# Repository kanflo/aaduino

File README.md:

# The AAduino

### News! Don't miss the successor of the AAduino, the [AAduino Zero](https://github.com/kanflo/aaduino-zero).

The AAduino is an wireless Arduino clone the size of an AA battery with Keystone battery terminals rotated 180° to act as positive and negative terminals. It is meant to go inside a 3xAA battery holder creating a very small wireless node.

Powered by an ATMega328p, it is fitted with an RFM69CW companion, two DS18B20 temperature sensors and an indicator LED.

Included in this repository is the schematics, bill of material and a sample program to test the hardware.
If you want solder up one yourself you can buy most of what is needed through the links on the [Kitnic page](https://kitnic.it/boards/github.com/kanflo/aaduino).

If you are looking for an easy way to order the PCBs only, please order from [DirtyPCBs.com](http://dirtypcbs.com/view.php?share=18116&accesskey=5cb9ea9c4754e5c9102b4350393b244e) and I will receive a $1 credit :)

The accompanying blog post is [here](http://johan.kanflo.com/the-aaduino).

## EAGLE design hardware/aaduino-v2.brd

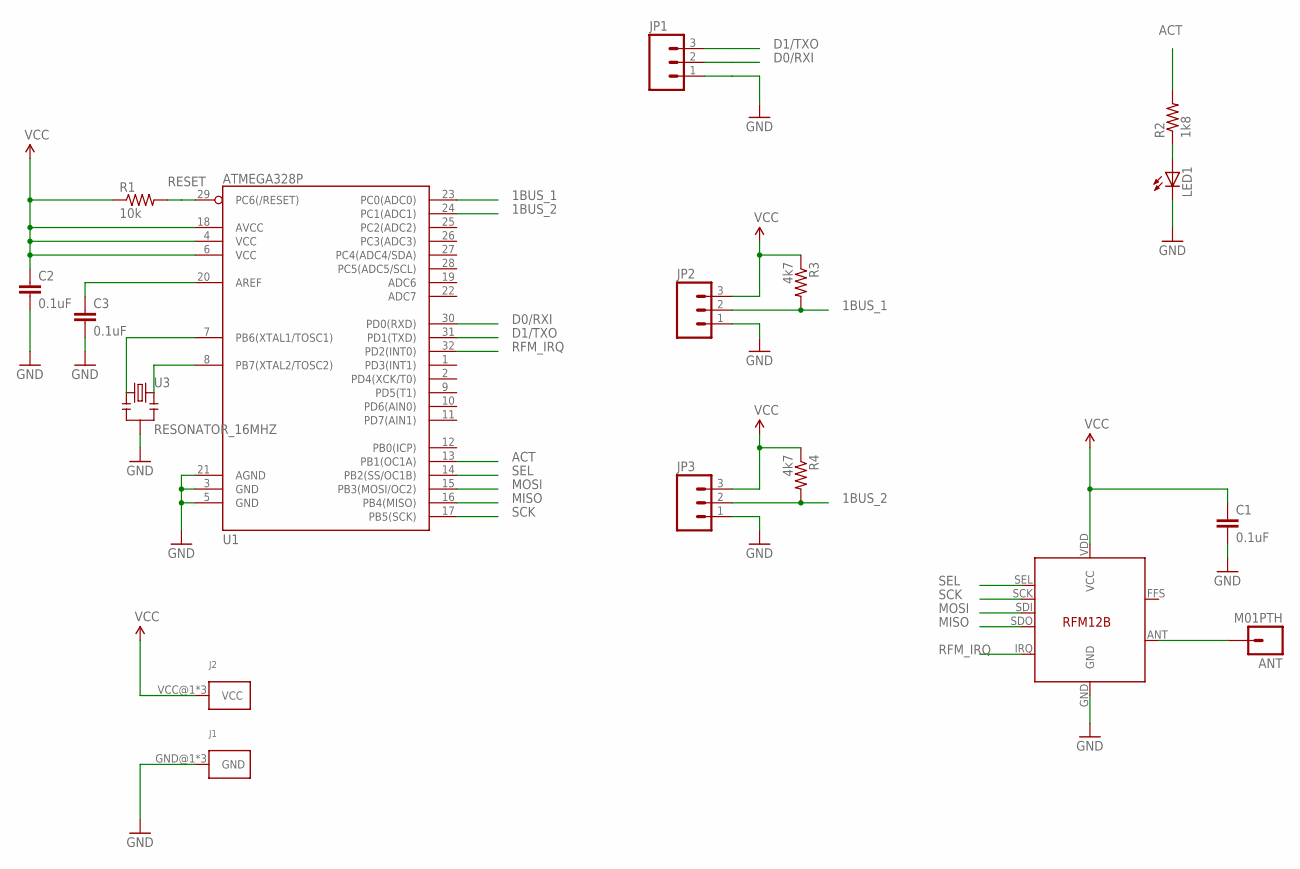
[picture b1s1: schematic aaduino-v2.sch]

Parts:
ANT: M01PTH; 1X01
C1, C2, C3: 0.1uF; 0603-CAP
J1: KEYSTONE-629; KEYSTONE_AA_AAA_BATTERY_TERMINAL-629
J2: KEYSTONE-637; KEYSTONE_AA_AAA_BATTERY_TERMINAL-637
JP1, JP2, JP3: M03PTH; 1X03
LED1: LED0603; LED-0603
R1: 10k; 0603-RES
R2: 1k8; 0603-RES
R3, R4: 4k7; 0603-RES
U1: ATMEGA328P; TQFP32-08
U2: RFM12B
U3: RESONATOR_16MHZ; RESONATOR_SMD

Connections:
1BUS_1: JP2.2, R3.2, U1.23 (PC0(ADC0))
1BUS_2: JP3.2, R4.2, U1.24 (PC1(ADC1))
ACT: R2.2, U1.13 (PB1(OC1A))
D0/RXI: JP1.2, U1.30 (PD0(RXD))
D1/TXO: JP1.3, U1.31 (PD1(TXD))
GND: C1.2, C2.2, C3.2, J1.GND@1, J1.GND@2, J1.GND@3, JP1.1, JP2.1, JP3.1, LED1.C, U1.3 (GND), U1.5 (GND), U1.21 (AGND), U2.GND, U3.2
MISO: U1.16 (PB4(MISO)), U2.SDO
MOSI: U1.15 (PB3(MOSI/OC2)), U2.SDI
unnamed: LED1.A, R2.1
unnamed: C3.1, U1.20 (AREF)
unnamed: U1.7 (PB6(XTAL1/TOSC1)), U3.1
unnamed: U1.8 (PB7(XTAL2/TOSC2)), U3.3
unnamed: ANT.1, U2.ANT
RESET: R1.2, U1.29 (PC6(/RESET))
RFM_IRQ: U1.32 (PD2(INT0)), U2.IRQ
SCK: U1.17 (PB5(SCK)), U2.SCK
SEL: U1.14 (PB2(SS/OC1B)), U2.SEL
VCC: C1.1, C2.1, J2.VCC@1, J2.VCC@2, J2.VCC@3, JP2.3, JP3.3, R1.1, R3.1, R4.1, U1.4 (VCC), U1.6 (VCC), U1.18 (AVCC), U2.VDD (VCC)

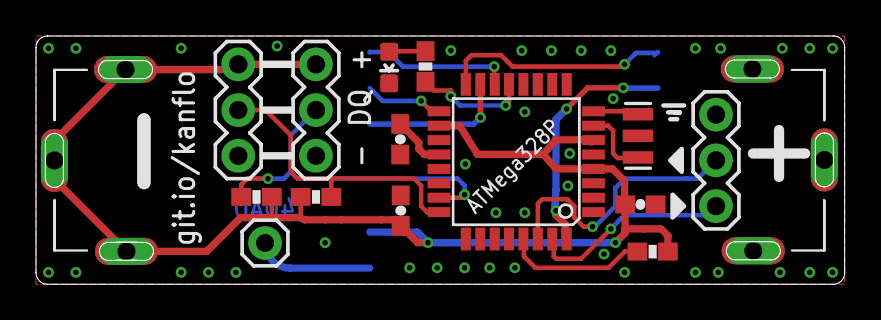
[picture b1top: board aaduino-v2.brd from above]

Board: 2 copper layers, 44.9 x 13.8 mm, 17 parts (1 on the bottom side), 18 nets.

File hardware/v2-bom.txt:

Part Value           Device                    Package                              Description           PROD_ID   VALUE     
ANT  M01PTH          M01PTH                    1X01                                 Header 1                                  
C1   0.1uF           0.1UF-25V(+80/-20%)(0603) 0603-CAP                             CAP-00810             CAP-00810 0.1uF     
C2   0.1uF           0.1UF-25V(+80/-20%)(0603) 0603-CAP                             CAP-00810             CAP-00810 0.1uF     
C3   0.1uF           0.1UF-25V(+80/-20%)(0603) 0603-CAP                             CAP-00810             CAP-00810 0.1uF     
J1   KEYSTONE-629    KEYSTONE-629              KEYSTONE_AA_AAA_BATTERY_TERMINAL-629 Keystone 629                              
J2   KEYSTONE-637    KEYSTONE-637              KEYSTONE_AA_AAA_BATTERY_TERMINAL-637 Keystone 637                              
JP1                  M03PTH                    1X03                                 Header 3                                  
JP2                  M03PTH                    1X03                                 Header 3                                  
JP3                  M03PTH                    1X03                                 Header 3                                  
LED1                 LED0603                   LED-0603                             LEDs                                      
R1   10k             RESISTOR0603-RES          0603-RES                             Resistor                                  
R2   1k8             RESISTOR0603-RES          0603-RES                             Resistor                                  
R3   4k7             RESISTOR0603-RES          0603-RES                             Resistor                                  
R4   4k7             RESISTOR0603-RES          0603-RES                             Resistor                                  
U1   ATMEGA328P      ATMEGA328_SMT             TQFP32-08                            32-Pin Atmega328 part IC-09069  ATMEGA328P
U2   RFM12B          RFM12B                    RFM12B                                                                         
U3   RESONATOR_8MHZ  RESONATOR_8MHZ            RESONATOR_SMD                                                                  

Oh, and if you want to build an AAduino, the markings for UART RX/TX got mixed up on the silk screen :-/

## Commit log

2016-04-13 Added image
2016-04-13 Added HW and SW
2016-04-20 Fixed typo
2016-08-18 Made compatible with kitnic.it
2016-08-31 Fixed up 1-click-bom
2016-08-31 Added Kitnic link to README
2016-09-19 Added thermometer demo
2016-09-20 Corrected RFM69C to RFM69CW
2016-10-12 Updated README with DirtyPCBs.com order link
2017-11-15 Added link to the AAduino Zero repo
2017-11-15 Added link to the AAduino Zero repo, take two

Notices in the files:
parts and their libraries:
SparkFun-DigitalIC: Licensing: Creative Commons ShareAlike 4.0 International - https://creativecommons.org/licenses/by-sa/4.0
